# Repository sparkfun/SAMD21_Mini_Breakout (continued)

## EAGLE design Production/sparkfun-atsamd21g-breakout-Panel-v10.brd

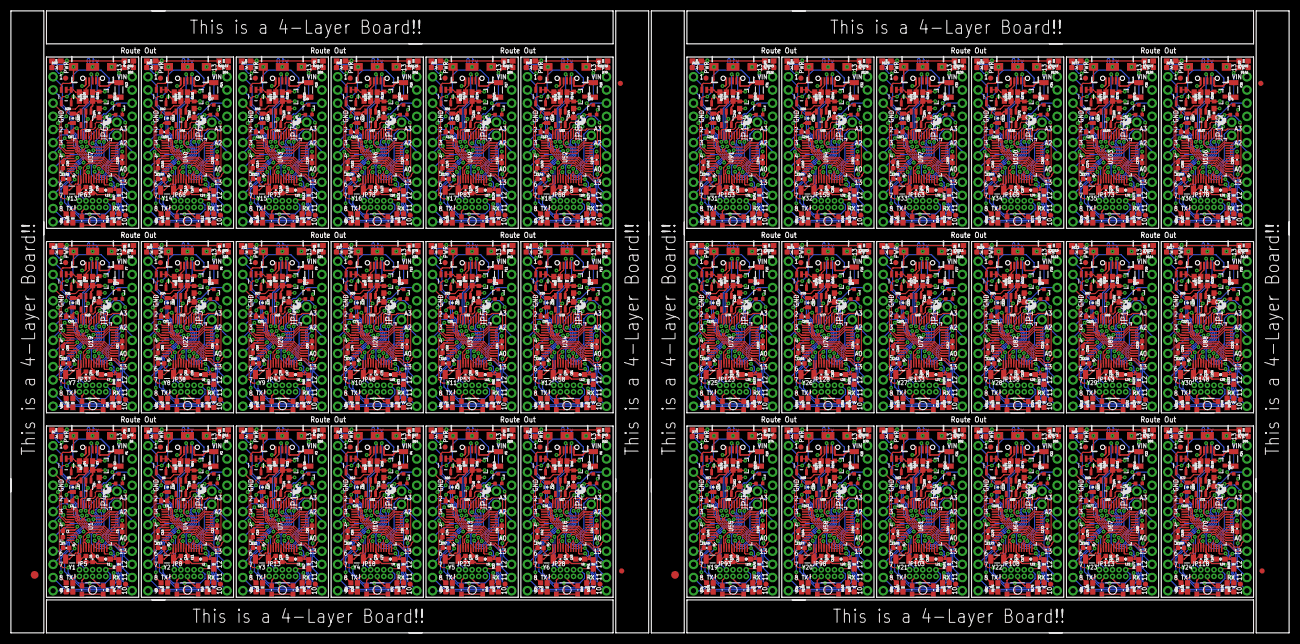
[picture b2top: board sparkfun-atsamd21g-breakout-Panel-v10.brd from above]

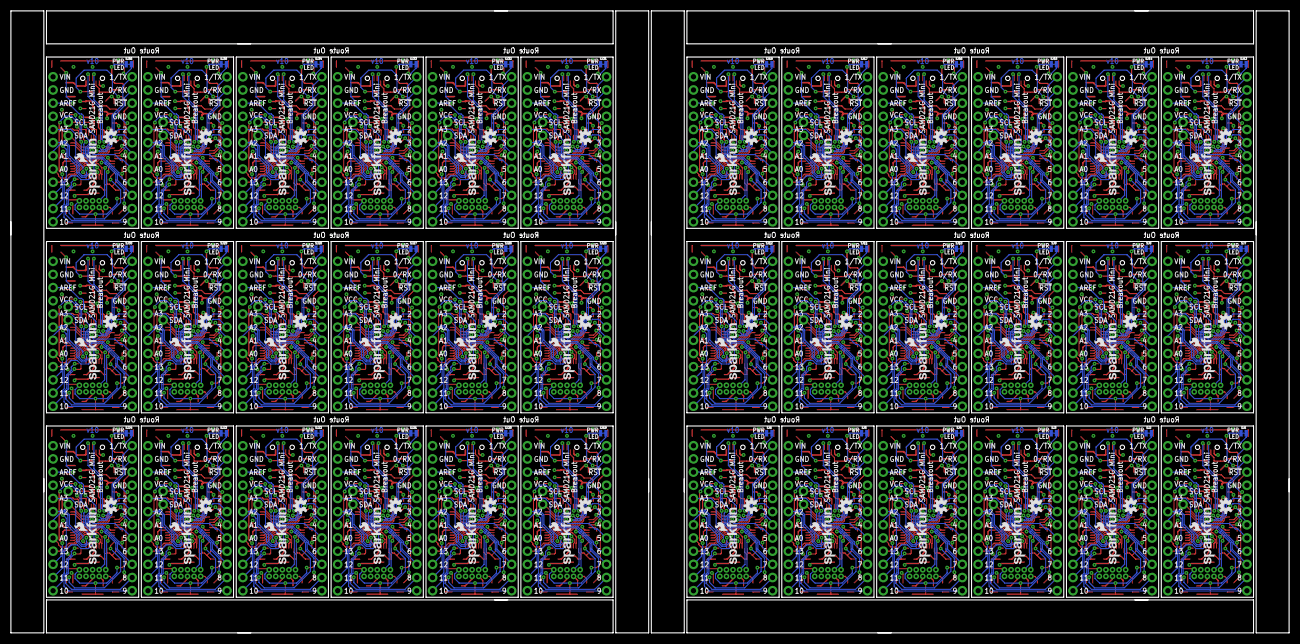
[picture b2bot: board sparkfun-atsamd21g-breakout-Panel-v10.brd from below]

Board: 4 copper layers, 246.4 x 119.9 mm, 1446 parts (108 on the bottom side), 1656 nets.

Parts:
C1, C2, C3, C4, C9, C10, C11, C12, C17, C18, C19, C20, C25, C26, C27, C28, C33, C34, C35, C36, C41, C42, C43, C44, C49, C50, C51, C52, C57, C58, C59, C60, C65, C66, C67, C68, C73, C74, C75, C76, C81, C82, C83, C84, C89, C90, C91, C92, C97, C98, C99, C100, C105, C106, C107, C108, C113, C114, C115, C116, C121, C122, C123, C124, C129, C130, C131, C132, C137, C138, C139, C140, C145, C146, C147, C148, C153, C154, C155, C156, C161, C162, C163, C164, C169, C170, C171, C172, C177, C178, C179, C180, C185, C186, C187, C188, C193, C194, C195, C196, C201, C202, C203, C204, C209, C210, C211, C212, C217, C218, C219, C220, C225, C226, C227, C228, C233, C234, C235, C236, C241, C242, C243, C244, C249, C250, C251, C252, C257, C258, C259, C260, C265, C266, C267, C268, C273, C274, C275, C276, C281, C282, C283, C284: 0.1uF; 0402-CAP
C5, C6, C13, C14, C21, C22, C29, C30, C37, C38, C45, C46, C53, C54, C61, C62, C69, C70, C77, C78, C85, C86, C93, C94, C101, C102, C109, C110, C117, C118, C125, C126, C133, C134, C141, C142, C149, C150, C157, C158, C165, C166, C173, C174, C181, C182, C189, C190, C197, C198, C205, C206, C213, C214, C221, C222, C229, C230, C237, C238, C245, C246, C253, C254, C261, C262, C269, C270, C277, C278, C285, C286: 15pF; 0402-CAP
C7, C15, C23, C31, C39, C47, C55, C63, C71, C79, C87, C95, C103, C111, C119, C127, C135, C143, C151, C159, C167, C175, C183, C191, C199, C207, C215, C223, C231, C239, C247, C255, C263, C271, C279, C287: 1.0uF; 0805-CAP
C8, C16, C24, C32, C40, C48, C56, C64, C72, C80, C88, C96, C104, C112, C120, C128, C136, C144, C152, C160, C168, C176, C184, C192, C200, C208, C216, C224, C232, C240, C248, C256, C264, C272, C280, C288: 2.2uF; 0603-CAP
D1, D7, D11, D15, D19, D23, D27, D31, D35, D39, D43, D47, D51, D55, D59, D63, D67, D71, D75, D79, D83, D87, D91, D95, D99, D103, D107, D111, D115, D119, D123, D127, D131, D135, D139, D143: GREEN; LED-0603
D2, D5, D9, D13, D17, D21, D25, D29, D33, D37, D41, D45, D49, D53, D57, D61, D65, D69, D73, D77, D81, D85, D89, D93, D97, D101, D105, D109, D113, D117, D121, D125, D129, D133, D137, D141: RED; LED-0603
D3, D6, D10, D14, D18, D22, D26, D30, D34, D38, D42, D46, D50, D54, D58, D62, D66, D70, D74, D78, D82, D86, D90, D94, D98, D102, D106, D110, D114, D118, D122, D126, D130, D134, D138, D142: BLUE; LED-0603
D4, D8, D12, D16, D20, D24, D28, D32, D36, D40, D44, D48, D52, D56, D60, D64, D68, D72, D76, D80, D84, D88, D92, D96, D100, D104, D108, D112, D116, D120, D124, D128, D132, D136, D140, D144: Yellow; LED-0603
E$1, E$4: FIDUCIAL-1.5X3
E$2, E$3, E$5, E$6: FIDUCIAL-1X2
F1, F2, F3, F4, F5, F6, F7, F8, F9, F10, F11, F12, F13, F14, F15, F16, F17, F18, F19, F20, F21, F22, F23, F24, F25, F26, F27, F28, F29, F30, F31, F32, F33, F34, F35, F36: 500mA; PTC-1206
FID1, FID2, FID3, FID4, FID5, FID6, FID7, FID8, FID9, FID10, FID11, FID12, FID13, FID14, FID15, FID16, FID17, FID18, FID19, FID20, FID21, FID22, FID23, FID24, FID25, FID26, FID27, FID28, FID29, FID30, FID31, FID32, FID33, FID34, FID35, FID36, FID37, FID38, FID39, FID40, FID41, FID42, FID43, FID44, FID45, FID46, FID47, FID48, FID49, FID50, FID51, FID52, FID53, FID54, FID55, FID56, FID57, FID58, FID59, FID60, FID61, FID62, FID63, FID64, FID65, FID66, FID67, FID68, FID69, FID70, FID71, FID72: FIDUCIAL1X2; FIDUCIAL-1X2
JP1, JP2, JP6, JP7, JP11, JP12, JP16, JP17, JP21, JP22, JP26, JP27, JP31, JP32, JP36, JP37, JP41, JP42, JP46, JP47, JP51, JP52, JP56, JP57, JP61, JP62, JP66, JP67, JP71, JP72, JP76, JP77, JP81, JP82, JP86, JP87, JP91, JP92, JP96, JP97, JP101, JP102, JP106, JP107, JP111, JP112, JP116, JP117, JP121, JP122, JP126, JP127, JP131, JP132, JP136, JP137, JP141, JP142, JP146, JP147, JP151, JP152, JP156, JP157, JP161, JP162, JP166, JP167, JP171, JP172, JP176, JP177: 1X12_NO_SILK
JP3, JP10, JP15, JP20, JP25, JP30, JP35, JP40, JP45, JP50, JP55, JP60, JP65, JP70, JP75, JP80, JP85, JP90, JP95, JP100, JP105, JP110, JP115, JP120, JP125, JP130, JP135, JP140, JP145, JP150, JP155, JP160, JP165, JP170, JP175, JP180: USB-AB-MICRO-SMD_V03
JP4, JP9, JP14, JP19, JP24, JP29, JP34, JP39, JP44, JP49, JP54, JP59, JP64, JP69, JP74, JP79, JP84, JP89, JP94, JP99, JP104, JP109, JP114, JP119, JP124, JP129, JP134, JP139, JP144, JP149, JP154, JP159, JP164, JP169, JP174, JP179: 1X02_NO_SILK
JP5, JP8, JP13, JP18, JP23, JP28, JP33, JP38, JP43, JP48, JP53, JP58, JP63, JP68, JP73, JP78, JP83, JP88, JP93, JP98, JP103, JP108, JP113, JP118, JP123, JP128, JP133, JP138, JP143, JP148, JP153, JP158, JP163, JP168, JP173, JP178: CORTEX_DEBUGPTH; 2X5-PTH-1.27MM
L1, L2, L3, L4, L5, L6, L7, L8, L9, L10, L11, L12, L13, L14, L15, L16, L17, L18, L19, L20, L21, L22, L23, L24, L25, L26, L27, L28, L29, L30, L31, L32, L33, L34, L35, L36: FB - 30Ohm; 0603
LOGO1, LOGO4, LOGO7, LOGO10, LOGO13, LOGO16, LOGO19, LOGO22, LOGO25, LOGO28, LOGO31, LOGO34, LOGO37, LOGO40, LOGO43, LOGO46, LOGO49, LOGO52, LOGO55, LOGO58, LOGO61, LOGO64, LOGO67, LOGO70, LOGO73, LOGO76, LOGO79, LOGO82, LOGO85, LOGO88, LOGO91, LOGO94, LOGO97, LOGO100, LOGO103, LOGO106: SFE_LOGO_FLAME.1_INCH; SFE_LOGO_FLAME_.1
LOGO2, LOGO5, LOGO8, LOGO11, LOGO14, LOGO17, LOGO20, LOGO23, LOGO26, LOGO29, LOGO32, LOGO35, LOGO38, LOGO41, LOGO44, LOGO47, LOGO50, LOGO53, LOGO56, LOGO59, LOGO62, LOGO65, LOGO68, LOGO71, LOGO74, LOGO77, LOGO80, LOGO83, LOGO86, LOGO89, LOGO92, LOGO95, LOGO98, LOGO101, LOGO104, LOGO107: OSHW-LOGOS; OSHW-LOGO-S
LOGO3, LOGO6, LOGO9, LOGO12, LOGO15, LOGO18, LOGO21, LOGO24, LOGO27, LOGO30, LOGO33, LOGO36, LOGO39, LOGO42, LOGO45, LOGO48, LOGO51, LOGO54, LOGO57, LOGO60, LOGO63, LOGO66, LOGO69, LOGO72, LOGO75, LOGO78, LOGO81, LOGO84, LOGO87, LOGO90, LOGO93, LOGO96, LOGO99, LOGO102, LOGO105, LOGO108: SFE_LOGO_NAME_FLAME.1_INCH; SFE_LOGO_NAME_FLAME_.1
Q1, Q3, Q5, Q7, Q9, Q11, Q13, Q15, Q17, Q19, Q21, Q23, Q25, Q27, Q29, Q31, Q33, Q35, Q37, Q39, Q41, Q43, Q45, Q47, Q49, Q51, Q53, Q55, Q57, Q59, Q61, Q63, Q65, Q67, Q69, Q71: 2N7002PW; SOT323
Q2, Q4, Q6, Q8, Q10, Q12, Q14, Q16, Q18, Q20, Q22, Q24, Q26, Q28, Q30, Q32, Q34, Q36, Q38, Q40, Q42, Q44, Q46, Q48, Q50, Q52, Q54, Q56, Q58, Q60, Q62, Q64, Q66, Q68, Q70, Q72: 2.5A/30V; SOT23-3
R1, R9, R17, R25, R33, R41, R49, R57, R65, R73, R81, R89, R97, R105, R113, R121, R129, R137, R145, R153, R161, R169, R177, R185, R193, R201, R209, R217, R225, R233, R241, R249, R257, R265, R273, R281: 10K; 0603-RES
R2, R3, R5, R6, R8, R10, R11, R13, R15, R16, R18, R19, R21, R23, R24, R26, R27, R29, R31, R32, R34, R35, R37, R39, R40, R42, R43, R45, R47, R48, R50, R51, R53, R55, R56, R58, R59, R61, R63, R64, R66, R67, R69, R71, R72, R74, R75, R77, R79, R80, R82, R83, R85, R87, R88, R90, R91, R93, R95, R96, R98, R99, R101, R103, R104, R106, R107, R109, R111, R112, R114, R115, R117, R119, R120, R122, R123, R125, R127, R128, R130, R131, R133, R135, R136, R138, R139, R141, R143, R144, R146, R147, R149, R151, R152, R154, R155, R157, R159, R160, R162, R163, R165, R167, R168, R170, R171, R173, R175, R176, R178, R179, R181, R183, R184, R186, R187, R189, R191, R192, R194, R195, R197, R199, R200, R202, R203, R205, R207, R208, R210, R211, R213, R215, R216, R218, R219, R221, R223, R224, R226, R227, R229, R231, R232, R234, R235, R237, R239, R240, R242, R243, R245, R247, R248, R250, R251, R253, R255, R256, R258, R259, R261, R263, R264, R266, R267, R269, R271, R272, R274, R275, R277, R279, R280, R282, R283, R285, R287, R288: 330; 0603-RES
R4, R12, R20, R28, R36, R44, R52, R60, R68, R76, R84, R92, R100, R108, R116, R124, R132, R140, R148, R156, R164, R172, R180, R188, R196, R204, R212, R220, R228, R236, R244, R252, R260, R268, R276, R284: 100k; 0603-RES
R7, R14, R22, R30, R38, R46, R54, R62, R70, R78, R86, R94, R102, R110, R118, R126, R134, R142, R150, R158, R166, R174, R182, R190, R198, R206, R214, R222, R230, R238, R246, R254, R262, R270, R278, R286: 47K; 0603-RES
S1, S2, S3, S4, S5, S6, S7, S8, S9, S10, S11, S12, S13, S14, S15, S16, S17, S18, S19, S20, S21, S22, S23, S24, S25, S26, S27, S28, S29, S30, S31, S32, S33, S34, S35, S36: RESET; TACTILE_SWITCH_SMD_4.6X2.8MM
SJ1, SJ2, SJ3, SJ4, SJ5, SJ6, SJ7, SJ8, SJ9, SJ10, SJ11, SJ12, SJ13, SJ14, SJ15, SJ16, SJ17, SJ18, SJ19, SJ20, SJ21, SJ22, SJ23, SJ24, SJ25, SJ26, SJ27, SJ28, SJ29, SJ30, SJ31, SJ32, SJ33, SJ34, SJ35, SJ36: PWR-LED; PAD-JUMPER-2-NC_BY_TRACE_NO_SILK
U1, U4, U7, U10, U13, U16, U19, U22, U25, U28, U31, U34, U37, U40, U43, U46, U49, U52, U55, U58, U61, U64, U67, U70, U73, U76, U79, U82, U85, U88, U91, U94, U97, U100, U103, U106: ATSAMD21G-A; TQFP-48
U2, U5, U8, U11, U14, U17, U20, U23, U26, U29, U32, U35, U38, U41, U44, U47, U50, U53, U56, U59, U62, U65, U68, U71, U74, U77, U80, U83, U86, U89, U92, U95, U98, U101, U104, U107: 3.3V; SOT23-5
U3, U6, U9, U12, U15, U18, U21, U24, U27, U30, U33, U36, U39, U42, U45, U48, U51, U54, U57, U60, U63, U66, U69, U72, U75, U78, U81, U84, U87, U90, U93, U96, U99, U102, U105, U108: 74AHC1G125; SOT23-5
Y1, Y2, Y3, Y4, Y5, Y6, Y7, Y8, Y9, Y10, Y11, Y12, Y13, Y14, Y15, Y16, Y17, Y18, Y19, Y20, Y21, Y22, Y23, Y24, Y25, Y26, Y27, Y28, Y29, Y30, Y31, Y32, Y33, Y34, Y35, Y36: 32.768kHz; CRYSTAL-SMD-3.2X1.5MM

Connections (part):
3.3V: C1.1, C4.1, C8.1, JP2.4, JP5.1, L1.1, R1.2, R2.2, R3.2, R6.2, R8.2, U1.17, U1.36, U1.44, U2.5
3.3V1: C9.1, C12.1, C16.1, JP7.4, JP8.1, L2.1, R9.2, R10.2, R11.2, R15.2, R16.2, U4.17, U4.36, U4.44, U5.5
3.3V2: C17.1, C20.1, C24.1, JP12.4, JP13.1, L3.1, R17.2, R18.2, R19.2, R23.2, R24.2, U7.17, U7.36, U7.44, U8.5
3.3V3: C25.1, C28.1, C32.1, JP17.4, JP18.1, L4.1, R25.2, R26.2, R27.2, R31.2, R32.2, U10.17, U10.36, U10.44, U11.5
3.3V4: C33.1, C36.1, C40.1, JP22.4, JP23.1, L5.1, R33.2, R34.2, R35.2, R39.2, R40.2, U13.17, U13.36, U13.44, U14.5
3.3V5: C41.1, C44.1, C48.1, JP27.4, JP28.1, L6.1, R41.2, R42.2, R43.2, R47.2, R48.2, U16.17, U16.36, U16.44, U17.5
3.3V6: C49.1, C52.1, C56.1, JP32.4, JP33.1, L7.1, R49.2, R50.2, R51.2, R55.2, R56.2, U19.17, U19.36, U19.44, U20.5
3.3V7: C57.1, C60.1, C64.1, JP37.4, JP38.1, L8.1, R57.2, R58.2, R59.2, R63.2, R64.2, U22.17, U22.36, U22.44, U23.5
3.3V8: C65.1, C68.1, C72.1, JP42.4, JP43.1, L9.1, R65.2, R66.2, R67.2, R71.2, R72.2, U25.17, U25.36, U25.44, U26.5
3.3V9: C73.1, C76.1, C80.1, JP47.4, JP48.1, L10.1, R73.2, R74.2, R75.2, R79.2, R80.2, U28.17, U28.36, U28.44, U29.5
3.3V10: C81.1, C84.1, C88.1, JP52.4, JP53.1, L11.1, R81.2, R82.2, R83.2, R87.2, R88.2, U31.17, U31.36, U31.44, U32.5
3.3V11: C89.1, C92.1, C96.1, JP57.4, JP58.1, L12.1, R89.2, R90.2, R91.2, R95.2, R96.2, U34.17, U34.36, U34.44, U35.5
3.3V12: C97.1, C100.1, C104.1, JP62.4, JP63.1, L13.1, R97.2, R98.2, R99.2, R103.2, R104.2, U37.17, U37.36, U37.44, U38.5
3.3V13: C105.1, C108.1, C112.1, JP67.4, JP68.1, L14.1, R105.2, R106.2, R107.2, R111.2, R112.2, U40.17, U40.36, U40.44, U41.5
3.3V14: C113.1, C116.1, C120.1, JP72.4, JP73.1, L15.1, R113.2, R114.2, R115.2, R119.2, R120.2, U43.17, U43.36, U43.44, U44.5
3.3V15: C121.1, C124.1, C128.1, JP77.4, JP78.1, L16.1, R121.2, R122.2, R123.2, R127.2, R128.2, U46.17, U46.36, U46.44, U47.5
3.3V16: C129.1, C132.1, C136.1, JP82.4, JP83.1, L17.1, R129.2, R130.2, R131.2, R135.2, R136.2, U49.17, U49.36, U49.44, U50.5
3.3V17: C137.1, C140.1, C144.1, JP87.4, JP88.1, L18.1, R137.2, R138.2, R139.2, R143.2, R144.2, U52.17, U52.36, U52.44, U53.5
3.3V18: C145.1, C148.1, C152.1, JP92.4, JP93.1, L19.1, R145.2, R146.2, R147.2, R151.2, R152.2, U55.17, U55.36, U55.44, U56.5
3.3V19: C153.1, C156.1, C160.1, JP97.4, JP98.1, L20.1, R153.2, R154.2, R155.2, R159.2, R160.2, U58.17, U58.36, U58.44, U59.5
3.3V20: C161.1, C164.1, C168.1, JP102.4, JP103.1, L21.1, R161.2, R162.2, R163.2, R167.2, R168.2, U61.17, U61.36, U61.44, U62.5
3.3V21: C169.1, C172.1, C176.1, JP107.4, JP108.1, L22.1, R169.2, R170.2, R171.2, R175.2, R176.2, U64.17, U64.36, U64.44, U65.5
3.3V22: C177.1, C180.1, C184.1, JP112.4, JP113.1, L23.1, R177.2, R178.2, R179.2, R183.2, R184.2, U67.17, U67.36, U67.44, U68.5
3.3V23: C185.1, C188.1, C192.1, JP117.4, JP118.1, L24.1, R185.2, R186.2, R187.2, R191.2, R192.2, U70.17, U70.36, U70.44, U71.5
3.3V24: C193.1, C196.1, C200.1, JP122.4, JP123.1, L25.1, R193.2, R194.2, R195.2, R199.2, R200.2, U73.17, U73.36, U73.44, U74.5
3.3V25: C201.1, C204.1, C208.1, JP127.4, JP128.1, L26.1, R201.2, R202.2, R203.2, R207.2, R208.2, U76.17, U76.36, U76.44, U77.5
3.3V26: C209.1, C212.1, C216.1, JP132.4, JP133.1, L27.1, R209.2, R210.2, R211.2, R215.2, R216.2, U79.17, U79.36, U79.44, U80.5
3.3V27: C217.1, C220.1, C224.1, JP137.4, JP138.1, L28.1, R217.2, R218.2, R219.2, R223.2, R224.2, U82.17, U82.36, U82.44, U83.5
3.3V28: C225.1, C228.1, C232.1, JP142.4, JP143.1, L29.1, R225.2, R226.2, R227.2, R231.2, R232.2, U85.17, U85.36, U85.44, U86.5
3.3V29: C233.1, C236.1, C240.1, JP147.4, JP148.1, L30.1, R233.2, R234.2, R235.2, R239.2, R240.2, U88.17, U88.36, U88.44, U89.5
3.3V30: C241.1, C244.1, C248.1, JP152.4, JP153.1, L31.1, R241.2, R242.2, R243.2, R247.2, R248.2, U91.17, U91.36, U91.44, U92.5
3.3V31: C249.1, C252.1, C256.1, JP157.4, JP158.1, L32.1, R249.2, R250.2, R251.2, R255.2, R256.2, U94.17, U94.36, U94.44, U95.5
3.3V32: C257.1, C260.1, C264.1, JP162.4, JP163.1, L33.1, R257.2, R258.2, R259.2, R263.2, R264.2, U97.17, U97.36, U97.44, U98.5
3.3V33: C265.1, C268.1, C272.1, JP167.4, JP168.1, L34.1, R265.2, R266.2, R267.2, R271.2, R272.2, U100.17, U100.36, U100.44, U101.5
3.3V34: C273.1, C276.1, C280.1, JP172.4, JP173.1, L35.1, R273.2, R274.2, R275.2, R279.2, R280.2, U103.17, U103.36, U103.44, U104.5
3.3V35: C281.1, C284.1, C288.1, JP177.4, JP178.1, L36.1, R281.2, R282.2, R283.2, R287.2, R288.2, U106.17, U106.36, U106.44, U107.5
!RESET: JP1.10, JP5.10, R1.1, S1.3, S1.4, U1.40
!RESET1: JP6.10, JP8.10, R9.1, S2.3, S2.4, U4.40
!RESET2: JP11.10, JP13.10, R17.1, S3.3, S3.4, U7.40
!RESET3: JP16.10, JP18.10, R25.1, S4.3, S4.4, U10.40
!RESET4: JP21.10, JP23.10, R33.1, S5.3, S5.4, U13.40
!RESET5: JP26.10, JP28.10, R41.1, S6.3, S6.4, U16.40
!RESET6: JP31.10, JP33.10, R49.1, S7.3, S7.4, U19.40
!RESET7: JP36.10, JP38.10, R57.1, S8.3, S8.4, U22.40
!RESET8: JP41.10, JP43.10, R65.1, S9.3, S9.4, U25.40
!RESET9: JP46.10, JP48.10, R73.1, S10.3, S10.4, U28.40
!RESET10: JP51.10, JP53.10, R81.1, S11.3, S11.4, U31.40
!RESET11: JP56.10, JP58.10, R89.1, S12.3, S12.4, U34.40
!RESET12: JP61.10, JP63.10, R97.1, S13.3, S13.4, U37.40
!RESET13: JP66.10, JP68.10, R105.1, S14.3, S14.4, U40.40
!RESET14: JP71.10, JP73.10, R113.1, S15.3, S15.4, U43.40
!RESET15: JP76.10, JP78.10, R121.1, S16.3, S16.4, U46.40
!RESET16: JP81.10, JP83.10, R129.1, S17.3, S17.4, U49.40
!RESET17: JP86.10, JP88.10, R137.1, S18.3, S18.4, U52.40
!RESET18: JP91.10, JP93.10, R145.1, S19.3, S19.4, U55.40
!RESET19: JP96.10, JP98.10, R153.1, S20.3, S20.4, U58.40
!RESET20: JP101.10, JP103.10, R161.1, S21.3, S21.4, U61.40
!RESET21: JP106.10, JP108.10, R169.1, S22.3, S22.4, U64.40
!RESET22: JP111.10, JP113.10, R177.1, S23.3, S23.4, U67.40
!RESET23: JP116.10, JP118.10, R185.1, S24.3, S24.4, U70.40
!RESET24: JP121.10, JP123.10, R193.1, S25.3, S25.4, U73.40
!RESET25: JP126.10, JP128.10, R201.1, S26.3, S26.4, U76.40
!RESET26: JP131.10, JP133.10, R209.1, S27.3, S27.4, U79.40
!RESET27: JP136.10, JP138.10, R217.1, S28.3, S28.4, U82.40
!RESET28: JP141.10, JP143.10, R225.1, S29.3, S29.4, U85.40
!RESET29: JP146.10, JP148.10, R233.1, S30.3, S30.4, U88.40
!RESET30: JP151.10, JP153.10, R241.1, S31.3, S31.4, U91.40
!RESET31: JP156.10, JP158.10, R249.1, S32.3, S32.4, U94.40
!RESET32: JP161.10, JP163.10, R257.1, S33.3, S33.4, U97.40
!RESET33: JP166.10, JP168.10, R265.1, S34.3, S34.4, U100.40
!RESET34: JP171.10, JP173.10, R273.1, S35.3, S35.4, U103.40
!RESET35: JP176.10, JP178.10, R281.1, S36.3, S36.4, U106.40
A0: JP2.8, U1.3
A1: JP2.7, U1.7
A2: JP2.6, U1.8
A3: JP2.5, U1.9
A4: JP7.5, U4.9
A5: JP7.6, U4.8
A6: JP7.7, U4.7
A7: JP7.8, U4.3
A8: JP12.5, U7.9
A9: JP12.6, U7.8
A10: JP12.7, U7.7
A11: JP12.8, U7.3
A12: JP17.5, U10.9
A13: JP17.6, U10.8
A14: JP17.7, U10.7
A15: JP17.8, U10.3
A16: JP22.5, U13.9
A17: JP22.6, U13.8
A18: JP22.7, U13.7
A19: JP22.8, U13.3
A20: JP27.5, U16.9
A21: JP27.6, U16.8
A22: JP27.7, U16.7
A23: JP27.8, U16.3
A24: JP32.5, U19.9
A25: JP32.6, U19.8
A26: JP32.7, U19.7
A27: JP32.8, U19.3
A28: JP37.5, U22.9
A29: JP37.6, U22.8
A30: JP37.7, U22.7
A31: JP37.8, U22.3
A32: JP42.5, U25.9
A33: JP42.6, U25.8
A34: JP42.7, U25.7
A35: JP42.8, U25.3
A36: JP47.5, U28.9
A37: JP47.6, U28.8
A38: JP47.7, U28.7
A39: JP47.8, U28.3
A40: JP52.5, U31.9
A41: JP52.6, U31.8
A42: JP52.7, U31.7
A43: JP52.8, U31.3
A44: JP57.5, U34.9
A45: JP57.6, U34.8
A46: JP57.7, U34.7
A47: JP57.8, U34.3
A48: JP62.5, U37.9
A49: JP62.6, U37.8
A50: JP62.7, U37.7
A51: JP62.8, U37.3
A52: JP67.5, U40.9
A53: JP67.6, U40.8
A54: JP67.7, U40.7
A55: JP67.8, U40.3
A56: JP72.5, U43.9
A57: JP72.6, U43.8
A58: JP72.7, U43.7
A59: JP72.8, U43.3
A60: JP77.5, U46.9
A61: JP77.6, U46.8
A62: JP77.7, U46.7
A63: JP77.8, U46.3
A64: JP82.5, U49.9
A65: JP82.6, U49.8
A66: JP82.7, U49.7
A67: JP82.8, U49.3
A68: JP87.5, U52.9
A69: JP87.6, U52.8
A70: JP87.7, U52.7
A71: JP87.8, U52.3
A72: JP92.5, U55.9
A73: JP92.6, U55.8
A74: JP92.7, U55.7
A75: JP92.8, U55.3
A76: JP97.5, U58.9
A77: JP97.6, U58.8
A78: JP97.7, U58.7
A79: JP97.8, U58.3
A80: JP102.5, U61.9
A81: JP102.6, U61.8
A82: JP102.7, U61.7
A83: JP102.8, U61.3
A84: JP107.5, U64.9
A85: JP107.6, U64.8
A86: JP107.7, U64.7
A87: JP107.8, U64.3
A88: JP112.5, U67.9
A89: JP112.6, U67.8
A90: JP112.7, U67.7
A91: JP112.8, U67.3
A92: JP117.5, U70.9
A93: JP117.6, U70.8
A94: JP117.7, U70.7
A95: JP117.8, U70.3
A96: JP122.5, U73.9
A97: JP122.6, U73.8
A98: JP122.7, U73.7
A99: JP122.8, U73.3
A100: JP127.5, U76.9
A101: JP127.6, U76.8
A102: JP127.7, U76.7
A103: JP127.8, U76.3
A104: JP132.5, U79.9
A105: JP132.6, U79.8
A106: JP132.7, U79.7
A107: JP132.8, U79.3
A108: JP137.5, U82.9
A109: JP137.6, U82.8
A110: JP137.7, U82.7
A111: JP137.8, U82.3
A112: JP142.5, U85.9
A113: JP142.6, U85.8
A114: JP142.7, U85.7
A115: JP142.8, U85.3
A116: JP147.5, U88.9
A117: JP147.6, U88.8
A118: JP147.7, U88.7
A119: JP147.8, U88.3
A120: JP152.5, U91.9
A121: JP152.6, U91.8
A122: JP152.7, U91.7
A123: JP152.8, U91.3
A124: JP157.5, U94.9
A125: JP157.6, U94.8
A126: JP157.7, U94.7
A127: JP157.8, U94.3
A128: JP162.5, U97.9
A129: JP162.6, U97.8
A130: JP162.7, U97.7
A131: JP162.8, U97.3
A132: JP167.5, U100.9
A133: JP167.6, U100.8
A134: JP167.7, U100.7
A135: JP167.8, U100.3
A136: JP172.5, U103.9
A137: JP172.6, U103.8
A138: JP172.7, U103.7
A139: JP172.8, U103.3
A140: JP177.5, U106.9
A141: JP177.6, U106.8
A142: JP177.7, U106.7
A143: JP177.8, U106.3
AREF: JP2.3, U1.4
AREF1: JP7.3, U4.4
AREF2: JP12.3, U7.4
AREF3: JP17.3, U10.4
AREF4: JP22.3, U13.4
AREF5: JP27.3, U16.4
AREF6: JP32.3, U19.4
AREF7: JP37.3, U22.4
AREF8: JP42.3, U25.4
AREF9: JP47.3, U28.4
AREF10: JP52.3, U31.4
AREF11: JP57.3, U34.4
AREF12: JP62.3, U37.4
AREF13: JP67.3, U40.4
AREF14: JP72.3, U43.4
AREF15: JP77.3, U46.4
AREF16: JP82.3, U49.4
AREF17: JP87.3, U52.4
AREF18: JP92.3, U55.4
AREF19: JP97.3, U58.4
AREF20: JP102.3, U61.4
AREF21: JP107.3, U64.4
AREF22: JP112.3, U67.4
AREF23: JP117.3, U70.4
AREF24: JP122.3, U73.4
AREF25: JP127.3, U76.4
AREF26: JP132.3, U79.4
AREF27: JP137.3, U82.4
AREF28: JP142.3, U85.4
AREF29: JP147.3, U88.4
AREF30: JP152.3, U91.4
AREF31: JP157.3, U94.4
AREF32: JP162.3, U97.4
AREF33: JP167.3, U100.4
AREF34: JP172.3, U103.4
AREF35: JP177.3, U106.4
D0/RXI: JP1.11, U1.16
D0/RXI1: JP6.11, U4.16
D0/RXI2: JP11.11, U7.16
D0/RXI3: JP16.11, U10.16
D0/RXI4: JP21.11, U13.16
D0/RXI5: JP26.11, U16.16
D0/RXI6: JP31.11, U19.16
D0/RXI7: JP36.11, U22.16
D0/RXI8: JP41.11, U25.16
D0/RXI9: JP46.11, U28.16
D0/RXI10: JP51.11, U31.16
D0/RXI11: JP56.11, U34.16
D0/RXI12: JP61.11, U37.16
D0/RXI13: JP66.11, U40.16
D0/RXI14: JP71.11, U43.16
D0/RXI15: JP76.11, U46.16
D0/RXI16: JP81.11, U49.16
D0/RXI17: JP86.11, U52.16
D0/RXI18: JP91.11, U55.16
D0/RXI19: JP96.11, U58.16
D0/RXI20: JP101.11, U61.16
D0/RXI21: JP106.11, U64.16
D0/RXI22: JP111.11, U67.16
D0/RXI23: JP116.11, U70.16
D0/RXI24: JP121.11, U73.16
D0/RXI25: JP126.11, U76.16
D0/RXI26: JP131.11, U79.16
D0/RXI27: JP136.11, U82.16
D0/RXI28: JP141.11, U85.16
D0/RXI29: JP146.11, U88.16
D0/RXI30: JP151.11, U91.16
D0/RXI31: JP156.11, U94.16
D0/RXI32: JP161.11, U97.16
D0/RXI33: JP166.11, U100.16
D0/RXI34: JP171.11, U103.16
D0/RXI35: JP176.11, U106.16
D1: JP6.6, U4.13
D1/TXO: JP1.12, U1.15
D1/TXO1: JP6.12, U4.15
D1/TXO2: JP11.12, U7.15
D1/TXO3: JP16.12, U10.15
D1/TXO4: JP21.12, U13.15
D1/TXO5: JP26.12, U16.15
D1/TXO6: JP31.12, U19.15
D1/TXO7: JP36.12, U22.15
D1/TXO8: JP41.12, U25.15
D1/TXO9: JP46.12, U28.15
D1/TXO10: JP51.12, U31.15
D1/TXO11: JP56.12, U34.15
D1/TXO12: JP61.12, U37.15
D1/TXO13: JP66.12, U40.15
D1/TXO14: JP71.12, U43.15
D1/TXO15: JP76.12, U46.15
D1/TXO16: JP81.12, U49.15
D1/TXO17: JP86.12, U52.15
D1/TXO18: JP91.12, U55.15
D1/TXO19: JP96.12, U58.15
D1/TXO20: JP101.12, U61.15
D1/TXO21: JP106.12, U64.15
D1/TXO22: JP111.12, U67.15
D1/TXO23: JP116.12, U70.15
D1/TXO24: JP121.12, U73.15
D1/TXO25: JP126.12, U76.15
D1/TXO26: JP131.12, U79.15
D1/TXO27: JP136.12, U82.15
D1/TXO28: JP141.12, U85.15
D1/TXO29: JP146.12, U88.15
D1/TXO30: JP151.12, U91.15
D1/TXO31: JP156.12, U94.15
D1/TXO32: JP161.12, U97.15
D1/TXO33: JP166.12, U100.15
D1/TXO34: JP171.12, U103.15
D1/TXO35: JP176.12, U106.15
D2: JP1.8, U1.23
D3: JP1.7, U1.14
D4: JP1.6, U1.13
D5: JP1.5, U1.24
D6: JP1.4, U1.29
D7: JP1.3, U1.30
D8: JP1.2, U1.11
D9: JP1.1, U1.12
D10: JP6.7, U4.14
D10/SS: JP2.12, U1.27
D10/SS1: JP7.12, U4.27
D10/SS2: JP12.12, U7.27
D10/SS3: JP17.12, U10.27
D10/SS4: JP22.12, U13.27
D10/SS5: JP27.12, U16.27
D10/SS6: JP32.12, U19.27
D10/SS7: JP37.12, U22.27
D10/SS8: JP42.12, U25.27
D10/SS9: JP47.12, U28.27
D10/SS10: JP52.12, U31.27
D10/SS11: JP57.12, U34.27
D10/SS12: JP62.12, U37.27
D10/SS13: JP67.12, U40.27
D10/SS14: JP72.12, U43.27
D10/SS15: JP77.12, U46.27
D10/SS16: JP82.12, U49.27
D10/SS17: JP87.12, U52.27
D10/SS18: JP92.12, U55.27
D10/SS19: JP97.12, U58.27
D10/SS20: JP102.12, U61.27
D10/SS21: JP107.12, U64.27
D10/SS22: JP112.12, U67.27
D10/SS23: JP117.12, U70.27
D10/SS24: JP122.12, U73.27
D10/SS25: JP127.12, U76.27
D10/SS26: JP132.12, U79.27
D10/SS27: JP137.12, U82.27
D10/SS28: JP142.12, U85.27
D10/SS29: JP147.12, U88.27
D10/SS30: JP152.12, U91.27
D10/SS31: JP157.12, U94.27
D10/SS32: JP162.12, U97.27
D10/SS33: JP167.12, U100.27
D10/SS34: JP172.12, U103.27
D10/SS35: JP177.12, U106.27
D11: JP6.8, U4.23
D11/MOSI: JP2.11, U1.25
D11/MOSI1: JP7.11, U4.25
D11/MOSI2: JP12.11, U7.25
D11/MOSI3: JP17.11, U10.25
D11/MOSI4: JP22.11, U13.25
D11/MOSI5: JP27.11, U16.25
D11/MOSI6: JP32.11, U19.25
D11/MOSI7: JP37.11, U22.25
D11/MOSI8: JP42.11, U25.25
D11/MOSI9: JP47.11, U28.25
D11/MOSI10: JP52.11, U31.25
D11/MOSI11: JP57.11, U34.25
D11/MOSI12: JP62.11, U37.25
D11/MOSI13: JP67.11, U40.25
D11/MOSI14: JP72.11, U43.25
D11/MOSI15: JP77.11, U46.25
D11/MOSI16: JP82.11, U49.25
D11/MOSI17: JP87.11, U52.25
D11/MOSI18: JP92.11, U55.25
D11/MOSI19: JP97.11, U58.25
D11/MOSI20: JP102.11, U61.25
D11/MOSI21: JP107.11, U64.25
D11/MOSI22: JP112.11, U67.25
D11/MOSI23: JP117.11, U70.25
D11/MOSI24: JP122.11, U73.25
D11/MOSI25: JP127.11, U76.25
D11/MOSI26: JP132.11, U79.25
D11/MOSI27: JP137.11, U82.25
D11/MOSI28: JP142.11, U85.25
D11/MOSI29: JP147.11, U88.25
D11/MOSI30: JP152.11, U91.25
D11/MOSI31: JP157.11, U94.25
D11/MOSI32: JP162.11, U97.25
D11/MOSI33: JP167.11, U100.25
D11/MOSI34: JP172.11, U103.25
D11/MOSI35: JP177.11, U106.25
D12: JP6.5, U4.24
D12/MISO: JP2.10, U1.28
D12/MISO1: JP7.10, U4.28
D12/MISO2: JP12.10, U7.28
D12/MISO3: JP17.10, U10.28
D12/MISO4: JP22.10, U13.28
D12/MISO5: JP27.10, U16.28
D12/MISO6: JP32.10, U19.28
D12/MISO7: JP37.10, U22.28
D12/MISO8: JP42.10, U25.28
D12/MISO9: JP47.10, U28.28
D12/MISO10: JP52.10, U31.28
D12/MISO11: JP57.10, U34.28
D12/MISO12: JP62.10, U37.28
D12/MISO13: JP67.10, U40.28
D12/MISO14: JP72.10, U43.28
D12/MISO15: JP77.10, U46.28
D12/MISO16: JP82.10, U49.28
D12/MISO17: JP87.10, U52.28
D12/MISO18: JP92.10, U55.28
D12/MISO19: JP97.10, U58.28
D12/MISO20: JP102.10, U61.28
D12/MISO21: JP107.10, U64.28
D12/MISO22: JP112.10, U67.28
D12/MISO23: JP117.10, U70.28
D12/MISO24: JP122.10, U73.28
D12/MISO25: JP127.10, U76.28
D12/MISO26: JP132.10, U79.28
D12/MISO27: JP137.10, U82.28
D12/MISO28: JP142.10, U85.28
D12/MISO29: JP147.10, U88.28
D12/MISO30: JP152.10, U91.28
D12/MISO31: JP157.10, U94.28
D12/MISO32: JP162.10, U97.28
D12/MISO33: JP167.10, U100.28
D12/MISO34: JP172.10, U103.28
D12/MISO35: JP177.10, U106.28
D13: JP6.4, U4.29
D13/SCK: JP2.9, Q1.1, U1.26
D13/SCK1: JP7.9, Q3.1, U4.26
D13/SCK2: JP12.9, Q5.1, U7.26
D13/SCK3: JP17.9, Q7.1, U10.26
D13/SCK4: JP22.9, Q9.1, U13.26
D13/SCK5: JP27.9, Q11.1, U16.26
D13/SCK6: JP32.9, Q13.1, U19.26
D13/SCK7: JP37.9, Q15.1, U22.26
D13/SCK8: JP42.9, Q17.1, U25.26
D13/SCK9: JP47.9, Q19.1, U28.26
D13/SCK10: JP52.9, Q21.1, U31.26
D13/SCK11: JP57.9, Q23.1, U34.26
D13/SCK12: JP62.9, Q25.1, U37.26
D13/SCK13: JP67.9, Q27.1, U40.26
D13/SCK14: JP72.9, Q29.1, U43.26
D13/SCK15: JP77.9, Q31.1, U46.26
D13/SCK16: JP82.9, Q33.1, U49.26
D13/SCK17: JP87.9, Q35.1, U52.26
D13/SCK18: JP92.9, Q37.1, U55.26
D13/SCK19: JP97.9, Q39.1, U58.26
D13/SCK20: JP102.9, Q41.1, U61.26
D13/SCK21: JP107.9, Q43.1, U64.26
D13/SCK22: JP112.9, Q45.1, U67.26
D13/SCK23: JP117.9, Q47.1, U70.26
D13/SCK24: JP122.9, Q49.1, U73.26
D13/SCK25: JP127.9, Q51.1, U76.26
D13/SCK26: JP132.9, Q53.1, U79.26
D13/SCK27: JP137.9, Q55.1, U82.26
D13/SCK28: JP142.9, Q57.1, U85.26
D13/SCK29: JP147.9, Q59.1, U88.26
D13/SCK30: JP152.9, Q61.1, U91.26
D13/SCK31: JP157.9, Q63.1, U94.26
D13/SCK32: JP162.9, Q65.1, U97.26
D13/SCK33: JP167.9, Q67.1, U100.26
D13/SCK34: JP172.9, Q69.1, U103.26
D13/SCK35: JP177.9, Q71.1, U106.26
D14: JP6.3, U4.30
D15: JP6.2, U4.11
D16: JP6.1, U4.12
D17: JP11.6, U7.13
D18: JP11.7, U7.14
D19: JP11.8, U7.23
D20: JP11.5, U7.24
D21: JP11.4, U7.29
D22: JP11.3, U7.30
D23: JP11.2, U7.11
D24: JP11.1, U7.12
D25: JP16.6, U10.13
D26: JP16.7, U10.14
D27: JP16.8, U10.23
D28: JP16.5, U10.24
D29: JP16.4, U10.29
D30: JP16.3, U10.30
D31: JP16.2, U10.11
D32: JP16.1, U10.12
D33: JP21.6, U13.13
D34: JP21.7, U13.14
D35: JP21.8, U13.23
D36: JP21.5, U13.24
D37: JP21.4, U13.29
D38: JP21.3, U13.30
D39: JP21.2, U13.11
D40: JP21.1, U13.12
D41: JP26.6, U16.13
D42: JP26.7, U16.14
D43: JP26.8, U16.23
D44: JP26.5, U16.24
D45: JP26.4, U16.29
D46: JP26.3, U16.30
D47: JP26.2, U16.11
D48: JP26.1, U16.12
D49: JP31.6, U19.13
D50: JP31.7, U19.14
D51: JP31.8, U19.23
D52: JP31.5, U19.24
D53: JP31.4, U19.29
D54: JP31.3, U19.30
D55: JP31.2, U19.11
D56: JP31.1, U19.12
D57: JP36.6, U22.13
D58: JP36.7, U22.14
D59: JP36.8, U22.23
D60: JP36.5, U22.24
D61: JP36.4, U22.29
D62: JP36.3, U22.30
D63: JP36.2, U22.11
D64: JP36.1, U22.12
D65: JP41.6, U25.13
D66: JP41.7, U25.14
D67: JP41.8, U25.23
D68: JP41.5, U25.24
D69: JP41.4, U25.29
D70: JP41.3, U25.30
D71: JP41.2, U25.11
D72: JP41.1, U25.12
D73: JP46.6, U28.13
D74: JP46.7, U28.14
D75: JP46.8, U28.23
D76: JP46.5, U28.24
D77: JP46.4, U28.29
D78: JP46.3, U28.30
D79: JP46.2, U28.11
D80: JP46.1, U28.12
D81: JP51.6, U31.13
D82: JP51.7, U31.14
D83: JP51.8, U31.23
D84: JP51.5, U31.24
D85: JP51.4, U31.29
D86: JP51.3, U31.30
D87: JP51.2, U31.11
D88: JP51.1, U31.12
D89: JP56.6, U34.13
D90: JP56.7, U34.14
D91: JP56.8, U34.23
D92: JP56.5, U34.24
D93: JP56.4, U34.29
D94: JP56.3, U34.30
D95: JP56.2, U34.11
D96: JP56.1, U34.12
D97: JP61.6, U37.13
D98: JP61.7, U37.14
D99: JP61.8, U37.23
D100: JP61.5, U37.24
D101: JP61.4, U37.29
D102: JP61.3, U37.30
D103: JP61.2, U37.11
D104: JP61.1, U37.12
D105: JP66.6, U40.13
D106: JP66.7, U40.14
D107: JP66.8, U40.23
D108: JP66.5, U40.24
D109: JP66.4, U40.29
D110: JP66.3, U40.30
D111: JP66.2, U40.11
D112: JP66.1, U40.12
D113: JP71.6, U43.13
D114: JP71.7, U43.14
D115: JP71.8, U43.23
D116: JP71.5, U43.24
D117: JP71.4, U43.29
D118: JP71.3, U43.30
D119: JP71.2, U43.11
D120: JP71.1, U43.12
D121: JP76.6, U46.13
D122: JP76.7, U46.14
D123: JP76.8, U46.23
D124: JP76.5, U46.24
D125: JP76.4, U46.29
D126: JP76.3, U46.30
D127: JP76.2, U46.11
D128: JP76.1, U46.12
D129: JP81.6, U49.13
D130: JP81.7, U49.14
D131: JP81.8, U49.23
D132: JP81.5, U49.24
D133: JP81.4, U49.29
D134: JP81.3, U49.30
D135: JP81.2, U49.11
D136: JP81.1, U49.12
D137: JP86.6, U52.13
D138: JP86.7, U52.14
D139: JP86.8, U52.23
D140: JP86.5, U52.24
D141: JP86.4, U52.29
D142: JP86.3, U52.30
D143: JP86.2, U52.11
D144: JP86.1, U52.12
D145: JP91.6, U55.13
D146: JP91.7, U55.14
D147: JP91.8, U55.23
D148: JP91.5, U55.24
D149: JP91.4, U55.29
D150: JP91.3, U55.30
D151: JP91.2, U55.11
D152: JP91.1, U55.12
D153: JP96.6, U58.13
D154: JP96.7, U58.14
D155: JP96.8, U58.23
D156: JP96.5, U58.24
D157: JP96.4, U58.29
D158: JP96.3, U58.30
D159: JP96.2, U58.11
D160: JP96.1, U58.12
D161: JP101.6, U61.13
D162: JP101.7, U61.14
D163: JP101.8, U61.23
D164: JP101.5, U61.24
D165: JP101.4, U61.29
D166: JP101.3, U61.30
D167: JP101.2, U61.11
D168: JP101.1, U61.12
D169: JP106.6, U64.13
D170: JP106.7, U64.14
D171: JP106.8, U64.23
D172: JP106.5, U64.24
D173: JP106.4, U64.29
D174: JP106.3, U64.30
D175: JP106.2, U64.11
D176: JP106.1, U64.12
D177: JP111.6, U67.13
D178: JP111.7, U67.14
D179: JP111.8, U67.23
D180: JP111.5, U67.24
D181: JP111.4, U67.29
D182: JP111.3, U67.30
D183: JP111.2, U67.11
D184: JP111.1, U67.12
D185: JP116.6, U70.13
D186: JP116.7, U70.14
D187: JP116.8, U70.23
D188: JP116.5, U70.24
D189: JP116.4, U70.29
D190: JP116.3, U70.30
D191: JP116.2, U70.11
D192: JP116.1, U70.12
D193: JP121.6, U73.13
D194: JP121.7, U73.14
D195: JP121.8, U73.23
D196: JP121.5, U73.24
D197: JP121.4, U73.29
D198: JP121.3, U73.30
D199: JP121.2, U73.11
D200: JP121.1, U73.12
D201: JP126.6, U76.13
D202: JP126.7, U76.14
D203: JP126.8, U76.23
D204: JP126.5, U76.24
D205: JP126.4, U76.29
D206: JP126.3, U76.30
D207: JP126.2, U76.11
D208: JP126.1, U76.12
D209: JP131.6, U79.13
D210: JP131.7, U79.14
D211: JP131.8, U79.23
D212: JP131.5, U79.24
D213: JP131.4, U79.29
D214: JP131.3, U79.30
D215: JP131.2, U79.11
D216: JP131.1, U79.12
D217: JP136.6, U82.13
D218: JP136.7, U82.14
D219: JP136.8, U82.23
D220: JP136.5, U82.24
D221: JP136.4, U82.29
D222: JP136.3, U82.30
D223: JP136.2, U82.11
D224: JP136.1, U82.12
D225: JP141.6, U85.13
D226: JP141.7, U85.14
D227: JP141.8, U85.23
D228: JP141.5, U85.24
D229: JP141.4, U85.29
D230: JP141.3, U85.30
D231: JP141.2, U85.11
D232: JP141.1, U85.12
D233: JP146.6, U88.13
D234: JP146.7, U88.14
D235: JP146.8, U88.23
D236: JP146.5, U88.24
D237: JP146.4, U88.29
D238: JP146.3, U88.30
D239: JP146.2, U88.11
D240: JP146.1, U88.12
D241: JP151.6, U91.13
D242: JP151.7, U91.14
D243: JP151.8, U91.23
D244: JP151.5, U91.24
D245: JP151.4, U91.29
D246: JP151.3, U91.30
D247: JP151.2, U91.11
D248: JP151.1, U91.12
D249: JP156.6, U94.13
D250: JP156.7, U94.14
D251: JP156.8, U94.23
D252: JP156.5, U94.24
D253: JP156.4, U94.29
D254: JP156.3, U94.30
D255: JP156.2, U94.11
D256: JP156.1, U94.12
D257: JP161.6, U97.13
D258: JP161.7, U97.14
D259: JP161.8, U97.23
D260: JP161.5, U97.24
D261: JP161.4, U97.29
D262: JP161.3, U97.30
D263: JP161.2, U97.11
D264: JP161.1, U97.12
D265: JP166.6, U100.13
D266: JP166.7, U100.14
D267: JP166.8, U100.23
D268: JP166.5, U100.24
D269: JP166.4, U100.29
D270: JP166.3, U100.30
D271: JP166.2, U100.11
D272: JP166.1, U100.12
D273: JP171.6, U103.13
D274: JP171.7, U103.14
D275: JP171.8, U103.23
D276: JP171.5, U103.24
D277: JP171.4, U103.29
D278: JP171.3, U103.30
D279: JP171.2, U103.11
D280: JP171.1, U103.12
D281: JP176.6, U106.13
D282: JP176.7, U106.14
D283: JP176.8, U106.23
D284: JP176.5, U106.24
D285: JP176.4, U106.29
D286: JP176.3, U106.30
D287: JP176.2, U106.11
D288: JP176.1, U106.12
GND: C1.2, C2.2, C3.2, C4.2, C5.1, C6.2, C7.2, C8.2, JP1.9, JP2.2, JP3.GND1, JP3.SHIELD1, JP3.SHIELD2, JP3.SHIELD3, JP5.3, JP5.5, Q1.2, S1.1, S1.2, SJ1.1, U1.5, U1.18, U1.35, U1.42, U2.2, U3.3
GND1: C9.2, C10.2, C11.2, C12.2, C13.1, C14.2, C15.2, C16.2, JP6.9, JP7.2, JP8.3, JP8.5, JP10.GND1, JP10.SHIELD1, JP10.SHIELD2, JP10.SHIELD3, Q3.2, S2.1, S2.2, SJ2.1, U4.5, U4.18, U4.35, U4.42, U5.2, U6.3
GND2: C17.2, C18.2, C19.2, C20.2, C21.1, C22.2, C23.2, C24.2, JP11.9, JP12.2, JP13.3, JP13.5, JP15.GND1, JP15.SHIELD1, JP15.SHIELD2, JP15.SHIELD3, Q5.2, S3.1, S3.2, SJ3.1, U7.5, U7.18, U7.35, U7.42, U8.2, U9.3
GND3: C25.2, C26.2, C27.2, C28.2, C29.1, C30.2, C31.2, C32.2, JP16.9, JP17.2, JP18.3, JP18.5, JP20.GND1, JP20.SHIELD1, JP20.SHIELD2, JP20.SHIELD3, Q7.2, S4.1, S4.2, SJ4.1, U10.5, U10.18, U10.35, U10.42, U11.2, U12.3
GND4: C33.2, C34.2, C35.2, C36.2, C37.1, C38.2, C39.2, C40.2, JP21.9, JP22.2, JP23.3, JP23.5, JP25.GND1, JP25.SHIELD1, JP25.SHIELD2, JP25.SHIELD3, Q9.2, S5.1, S5.2, SJ5.1, U13.5, U13.18, U13.35, U13.42, U14.2, U15.3
GND5: C41.2, C42.2, C43.2, C44.2, C45.1, C46.2, C47.2, C48.2, JP26.9, JP27.2, JP28.3, JP28.5, JP30.GND1, JP30.SHIELD1, JP30.SHIELD2, JP30.SHIELD3, Q11.2, S6.1, S6.2, SJ6.1, U16.5, U16.18, U16.35, U16.42, U17.2, U18.3
GND6: C49.2, C50.2, C51.2, C52.2, C53.1, C54.2, C55.2, C56.2, JP31.9, JP32.2, JP33.3, JP33.5, JP35.GND1, JP35.SHIELD1, JP35.SHIELD2, JP35.SHIELD3, Q13.2, S7.1, S7.2, SJ7.1, U19.5, U19.18, U19.35, U19.42, U20.2, U21.3
GND7: C57.2, C58.2, C59.2, C60.2, C61.1, C62.2, C63.2, C64.2, JP36.9, JP37.2, JP38.3, JP38.5, JP40.GND1, JP40.SHIELD1, JP40.SHIELD2, JP40.SHIELD3, Q15.2, S8.1, S8.2, SJ8.1, U22.5, U22.18, U22.35, U22.42, U23.2, U24.3
GND8: C65.2, C66.2, C67.2, C68.2, C69.1, C70.2, C71.2, C72.2, JP41.9, JP42.2, JP43.3, JP43.5, JP45.GND1, JP45.SHIELD1, JP45.SHIELD2, JP45.SHIELD3, Q17.2, S9.1, S9.2, SJ9.1, U25.5, U25.18, U25.35, U25.42, U26.2, U27.3
GND9: C73.2, C74.2, C75.2, C76.2, C77.1, C78.2, C79.2, C80.2, JP46.9, JP47.2, JP48.3, JP48.5, JP50.GND1, JP50.SHIELD1, JP50.SHIELD2, JP50.SHIELD3, Q19.2, S10.1, S10.2, SJ10.1, U28.5, U28.18, U28.35, U28.42, U29.2, U30.3
GND10: C81.2, C82.2, C83.2, C84.2, C85.1, C86.2, C87.2, C88.2, JP51.9, JP52.2, JP53.3, JP53.5, JP55.GND1, JP55.SHIELD1, JP55.SHIELD2, JP55.SHIELD3, Q21.2, S11.1, S11.2, SJ11.1, U31.5, U31.18, U31.35, U31.42, U32.2, U33.3
GND11: C89.2, C90.2, C91.2, C92.2, C93.1, C94.2, C95.2, C96.2, JP56.9, JP57.2, JP58.3, JP58.5, JP60.GND1, JP60.SHIELD1, JP60.SHIELD2, JP60.SHIELD3, Q23.2, S12.1, S12.2, SJ12.1, U34.5, U34.18, U34.35, U34.42, U35.2, U36.3
GND12: C97.2, C98.2, C99.2, C100.2, C101.1, C102.2, C103.2, C104.2, JP61.9, JP62.2, JP63.3, JP63.5, JP65.GND1, JP65.SHIELD1, JP65.SHIELD2, JP65.SHIELD3, Q25.2, S13.1, S13.2, SJ13.1, U37.5, U37.18, U37.35, U37.42, U38.2, U39.3
GND13: C105.2, C106.2, C107.2, C108.2, C109.1, C110.2, C111.2, C112.2, JP66.9, JP67.2, JP68.3, JP68.5, JP70.GND1, JP70.SHIELD1, JP70.SHIELD2, JP70.SHIELD3, Q27.2, S14.1, S14.2, SJ14.1, U40.5, U40.18, U40.35, U40.42, U41.2, U42.3
GND14: C113.2, C114.2, C115.2, C116.2, C117.1, C118.2, C119.2, C120.2, JP71.9, JP72.2, JP73.3, JP73.5, JP75.GND1, JP75.SHIELD1, JP75.SHIELD2, JP75.SHIELD3, Q29.2, S15.1, S15.2, SJ15.1, U43.5, U43.18, U43.35, U43.42, U44.2, U45.3
GND15: C121.2, C122.2, C123.2, C124.2, C125.1, C126.2, C127.2, C128.2, JP76.9, JP77.2, JP78.3, JP78.5, JP80.GND1, JP80.SHIELD1, JP80.SHIELD2, JP80.SHIELD3, Q31.2, S16.1, S16.2, SJ16.1, U46.5, U46.18, U46.35, U46.42, U47.2, U48.3
GND16: C129.2, C130.2, C131.2, C132.2, C133.1, C134.2, C135.2, C136.2, JP81.9, JP82.2, JP83.3, JP83.5, JP85.GND1, JP85.SHIELD1, JP85.SHIELD2, JP85.SHIELD3, Q33.2, S17.1, S17.2, SJ17.1, U49.5, U49.18, U49.35, U49.42, U50.2, U51.3
GND17: C137.2, C138.2, C139.2, C140.2, C141.1, C142.2, C143.2, C144.2, JP86.9, JP87.2, JP88.3, JP88.5, JP90.GND1, JP90.SHIELD1, JP90.SHIELD2, JP90.SHIELD3, Q35.2, S18.1, S18.2, SJ18.1, U52.5, U52.18, U52.35, U52.42, U53.2, U54.3
GND18: C145.2, C146.2, C147.2, C148.2, C149.1, C150.2, C151.2, C152.2, JP91.9, JP92.2, JP93.3, JP93.5, JP95.GND1, JP95.SHIELD1, JP95.SHIELD2, JP95.SHIELD3, Q37.2, S19.1, S19.2, SJ19.1, U55.5, U55.18, U55.35, U55.42, U56.2, U57.3
GND19: C153.2, C154.2, C155.2, C156.2, C157.1, C158.2, C159.2, C160.2, JP96.9, JP97.2, JP98.3, JP98.5, JP100.GND1, JP100.SHIELD1, JP100.SHIELD2, JP100.SHIELD3, Q39.2, S20.1, S20.2, SJ20.1, U58.5, U58.18, U58.35, U58.42, U59.2, U60.3
GND20: C161.2, C162.2, C163.2, C164.2, C165.1, C166.2, C167.2, C168.2, JP101.9, JP102.2, JP103.3, JP103.5, JP105.GND1, JP105.SHIELD1, JP105.SHIELD2, JP105.SHIELD3, Q41.2, S21.1, S21.2, SJ21.1, U61.5, U61.18, U61.35, U61.42, U62.2, U63.3
GND21: C169.2, C170.2, C171.2, C172.2, C173.1, C174.2, C175.2, C176.2, JP106.9, JP107.2, JP108.3, JP108.5, JP110.GND1, JP110.SHIELD1, JP110.SHIELD2, JP110.SHIELD3, Q43.2, S22.1, S22.2, SJ22.1, U64.5, U64.18, U64.35, U64.42, U65.2, U66.3
GND22: C177.2, C178.2, C179.2, C180.2, C181.1, C182.2, C183.2, C184.2, JP111.9, JP112.2, JP113.3, JP113.5, JP115.GND1, JP115.SHIELD1, JP115.SHIELD2, JP115.SHIELD3, Q45.2, S23.1, S23.2, SJ23.1, U67.5, U67.18, U67.35, U67.42, U68.2, U69.3
GND23: C185.2, C186.2, C187.2, C188.2, C189.1, C190.2, C191.2, C192.2, JP116.9, JP117.2, JP118.3, JP118.5, JP120.GND1, JP120.SHIELD1, JP120.SHIELD2, JP120.SHIELD3, Q47.2, S24.1, S24.2, SJ24.1, U70.5, U70.18, U70.35, U70.42, U71.2, U72.3
GND24: C193.2, C194.2, C195.2, C196.2, C197.1, C198.2, C199.2, C200.2, JP121.9, JP122.2, JP123.3, JP123.5, JP125.GND1, JP125.SHIELD1, JP125.SHIELD2, JP125.SHIELD3, Q49.2, S25.1, S25.2, SJ25.1, U73.5, U73.18, U73.35, U73.42, U74.2, U75.3
GND25: C201.2, C202.2, C203.2, C204.2, C205.1, C206.2, C207.2, C208.2, JP126.9, JP127.2, JP128.3, JP128.5, JP130.GND1, JP130.SHIELD1, JP130.SHIELD2, JP130.SHIELD3, Q51.2, S26.1, S26.2, SJ26.1, U76.5, U76.18, U76.35, U76.42, U77.2, U78.3
GND26: C209.2, C210.2, C211.2, C212.2, C213.1, C214.2, C215.2, C216.2, JP131.9, JP132.2, JP133.3, JP133.5, JP135.GND1, JP135.SHIELD1, JP135.SHIELD2, JP135.SHIELD3, Q53.2, S27.1, S27.2, SJ27.1, U79.5, U79.18, U79.35, U79.42, U80.2, U81.3
GND27: C217.2, C218.2, C219.2, C220.2, C221.1, C222.2, C223.2, C224.2, JP136.9, JP137.2, JP138.3, JP138.5, JP140.GND1, JP140.SHIELD1, JP140.SHIELD2, JP140.SHIELD3, Q55.2, S28.1, S28.2, SJ28.1, U82.5, U82.18, U82.35, U82.42, U83.2, U84.3
GND28: C225.2, C226.2, C227.2, C228.2, C229.1, C230.2, C231.2, C232.2, JP141.9, JP142.2, JP143.3, JP143.5, JP145.GND1, JP145.SHIELD1, JP145.SHIELD2, JP145.SHIELD3, Q57.2, S29.1, S29.2, SJ29.1, U85.5, U85.18, U85.35, U85.42, U86.2, U87.3
GND29: C233.2, C234.2, C235.2, C236.2, C237.1, C238.2, C239.2, C240.2, JP146.9, JP147.2, JP148.3, JP148.5, JP150.GND1, JP150.SHIELD1, JP150.SHIELD2, JP150.SHIELD3, Q59.2, S30.1, S30.2, SJ30.1, U88.5, U88.18, U88.35, U88.42, U89.2, U90.3
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
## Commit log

2015-06-04 Initial commit of hardware.
2015-06-04 Adding SAMD21 Datasheet (long and short).
2015-06-08 Minor, pre-checklist modifications.
2015-06-08 Adding PROD_ID's to new parts.
2015-06-08 Removing (huge) datasheet.
2015-06-08 Renaming U4 to U3, adding tSilk to pin 11, dimension to .008in.
2015-06-09 Approving dimension DRC errors near button pads.
2015-06-10 created proto panel v01
2015-09-28 Moving silk. Swapping D4 and D2.
2015-09-28 Pulling buffer power up to RAW
2015-09-28 Dropping isolate on internal layers to 10mil
2015-09-28 Swapping MIC5205 Regulator out for AP2112K-3.3V
2015-09-29 Tweaking schematic and layout silk for checklist
2015-09-30 Sequentiallizing part names
2015-10-07 created panel v10
2015-11-12 Renaming hardware files to match product name.
2015-11-12 Adding v10 schematic.
2015-11-12 Adding graphic datasheets.
2015-11-12 Big readme update.
2015-11-12 Readme typo fix.
2015-11-16 Initial commit of SAMD21 Arduino bootloader
2015-12-06 Fix link to Atmel SAMD21 website.
2015-12-07 Adding License.md.
2019-02-20 Adds UF2 bootloader and Circuit Python build with a readme
2019-02-21 Updates readme for better clarity, and adds update bootloader binary file for those that prefer that over Arduino sketch
2022-10-21 Remove TC6 and TC7
    Confirmed issue in forum post: https://forum.sparkfun.com/viewtopic.php?f=145&t=57566&p=236540#p236540
    - Removed TC6 and TC7 from files
